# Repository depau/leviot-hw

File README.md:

# LevIoT - Air Purifier replacement controller

This is a replacement PCB based on ESP32 for the Levoit "True HEPA Air Purifier" Core 300, (Amazon model number: 817915027059).

It has currently not been tested yet, I just ordered it from a PCB manufacturer.

I spent around 30€ for 5 PCBs with most components pre-soldered by the PCB manufacturer, + around 13€ on AliExpress for the
push buttons, shift registers and PH connectors.

Touchpad springs and LEDs are going to be recovered from the original PCB.

## Taking the original board out

The top cover comes off by inserting a spudger tool between the top white and gray plastic parts.

The PCB is attached to the top plastic lid with some clips, and connected to the motor via a 6-pin JST-PH connector.

## Control board protocol

Pinout:

| Pin #   | Function   |
| ------- | ---------- |
| 1 (red) | VCC        |
| 2       | GND        |
| 3       | Speed 3    |
| 4       | Speed 2    |
| 5       | Speed 1    |
| 6       | Night mode |

The control board simply pulls one of the pins from 3 to 6 high with the other ones low to set the speed, with all low being "off".

The motor side seems to accept pretty much any voltage > 1V as long as the current is at least ~20 mA, though when using the original
board I measure 4V across the pin and ground - current should be around 80 mA.

You can test it by placing a 100 ohm resistor between 5V and one of the speed pins.

### Important safety notice

I'm not an electrical motor expert but I know that fans need to be started at the maximum speed from the off state in order to
prevent motor strain, overheating and fire hazards.

See this video about it by Technology Connections: https://www.youtube.com/watch?v=hQ3GW7lVBWY

A custom board firmware must kickstart the fan at maximum speed for ~1 sec after power on, then set it back to whatever speed
is desired.

The original board does this automatically.

## License

CERN Open Hardware License, strictly reciprocal.

## Disclaimer

I will not take any responsibility for broken air filters caused by modding or installing this custom PCB. You take your own
responsibility.

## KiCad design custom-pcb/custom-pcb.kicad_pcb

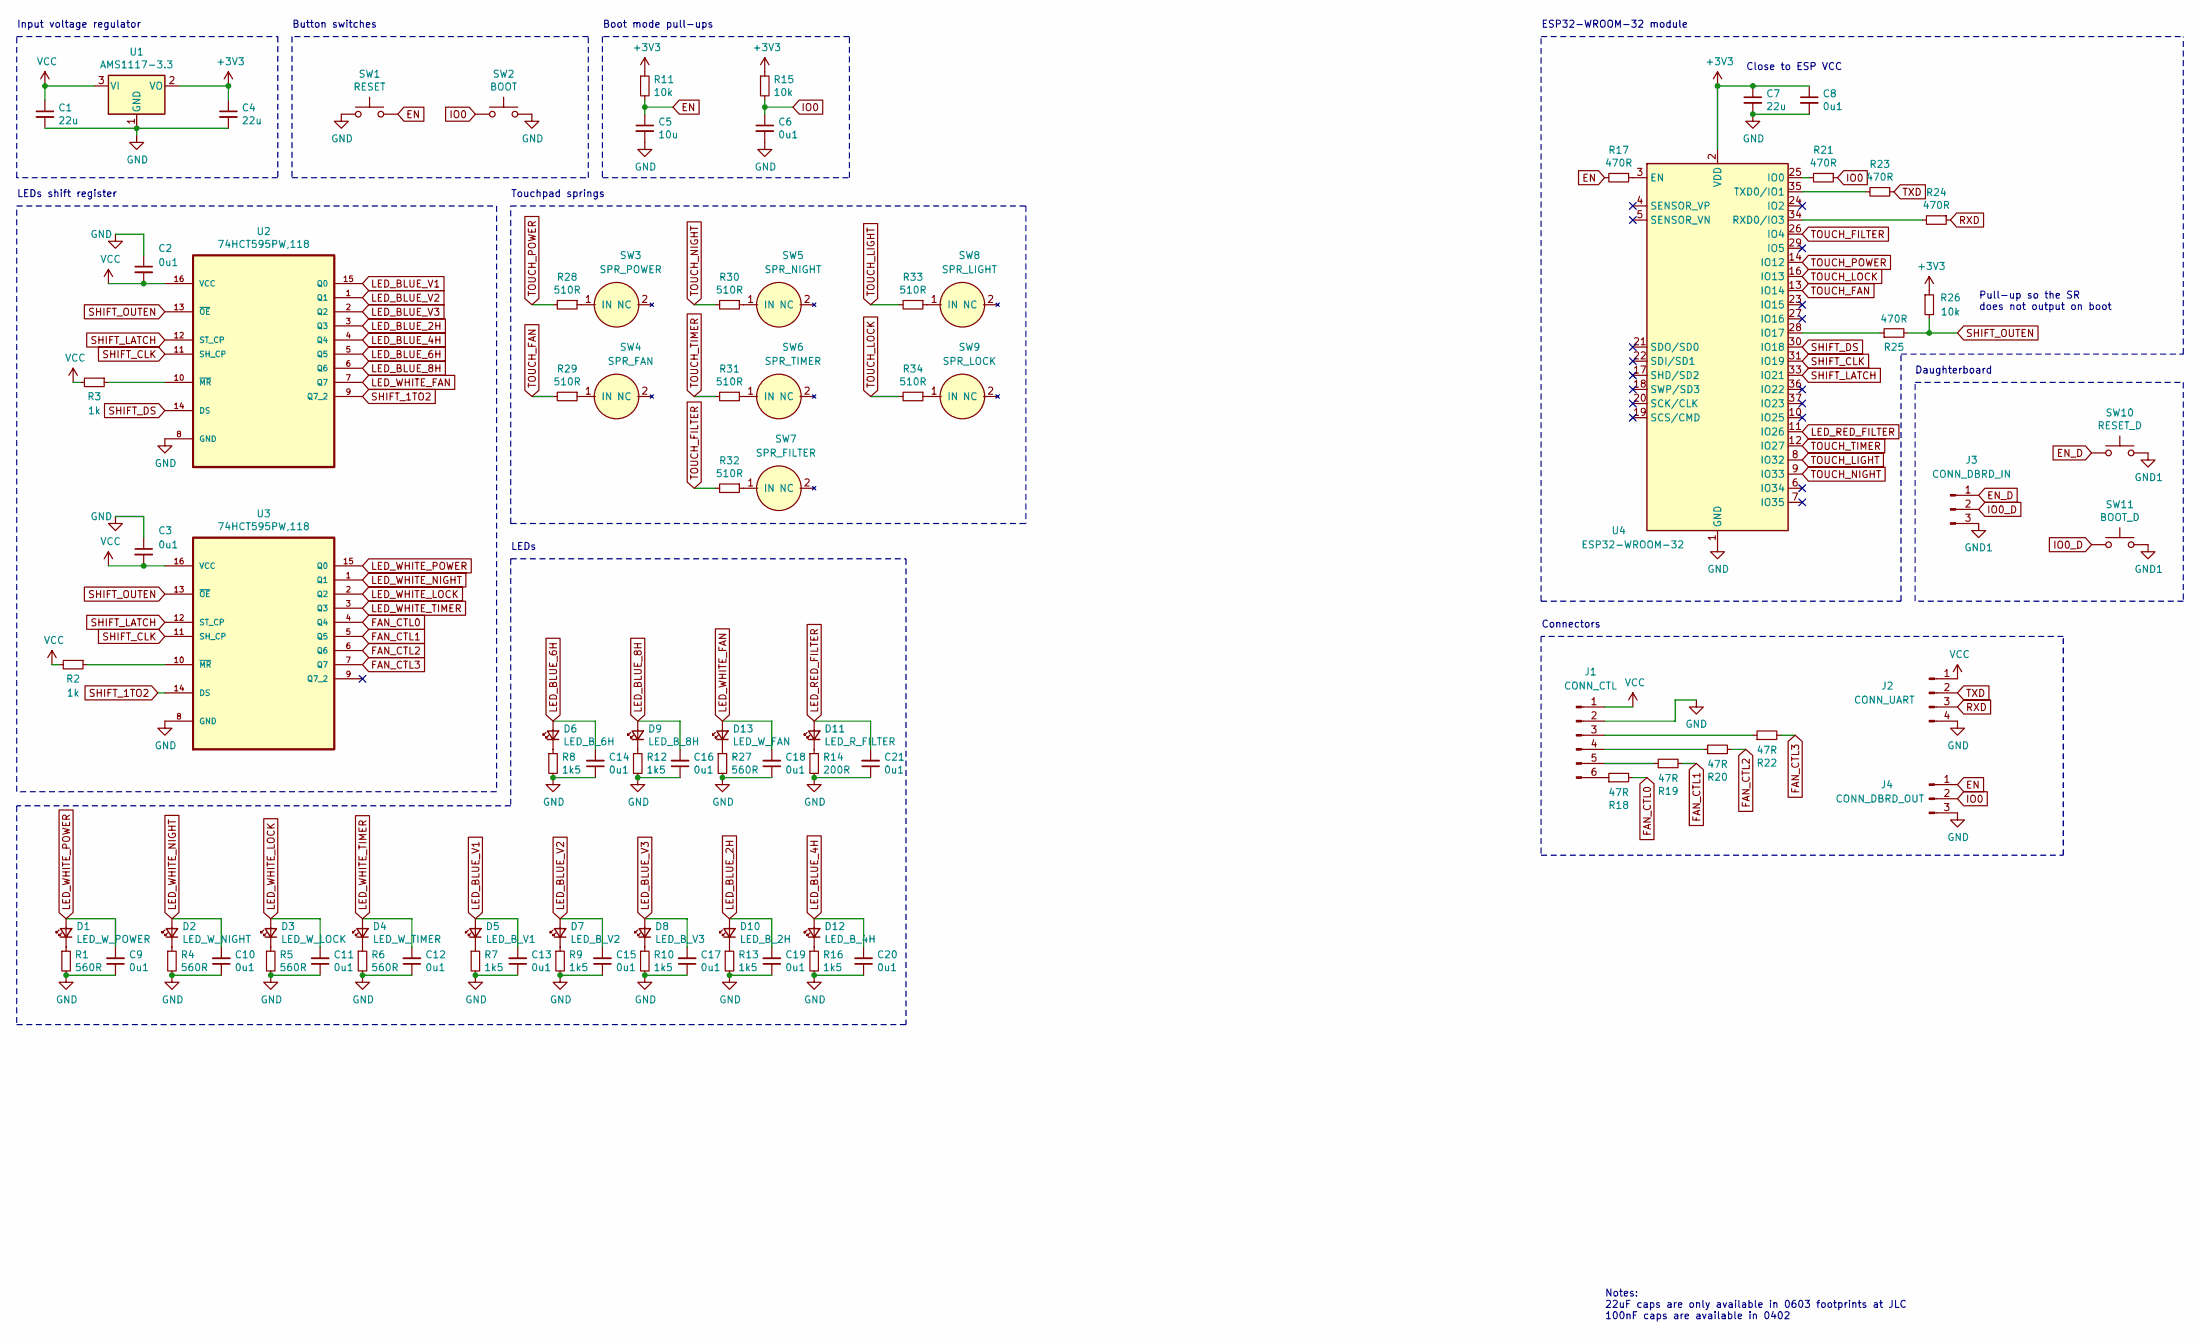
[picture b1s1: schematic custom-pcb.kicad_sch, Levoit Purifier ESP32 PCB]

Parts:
C1, C4, C7: 22u; C_0805_2012Metric; LCSC Part C45783
C2, C3, C8: 0u1; C_0805_2012Metric; LCSC Part C49678
C5: 10u; C_0402_1005Metric; LCSC Part C15525
C6: 0u1; C_0402_1005Metric; LCSC Part C1525
C9, C10, C11, C12, C13, C14, C15, C16, C17, C18, C19, C20, C21: 0u1; C_0402_1005Metric
D1: LED_W_POWER; LED_D5.0mm-centered; JLCPCB BOM 0
D2: LED_W_NIGHT; LED_D5.0mm-centered; JLCPCB BOM 0
D3: LED_W_LOCK; LED_D5.0mm-centered; JLCPCB BOM 0
D4: LED_W_TIMER; LED_D5.0mm-centered; JLCPCB BOM 0
D5: LED_B_V1; LED_0603_1608Metric_Pad1.05x0.95mm_HandSolder; JLCPCB BOM 0
D6: LED_B_6H; LED_0603_1608Metric_Pad1.05x0.95mm_HandSolder; JLCPCB BOM 0
D7: LED_B_V2; LED_0603_1608Metric_Pad1.05x0.95mm_HandSolder; JLCPCB BOM 0
D8: LED_B_V3; LED_0603_1608Metric_Pad1.05x0.95mm_HandSolder; JLCPCB BOM 0
D9: LED_B_8H; LED_0603_1608Metric_Pad1.05x0.95mm_HandSolder; JLCPCB BOM 0
D10: LED_B_2H; LED_0603_1608Metric_Pad1.05x0.95mm_HandSolder; JLCPCB BOM 0
D11: LED_R_FILTER; LED_D5.0mm-centered; JLCPCB BOM 0
D12: LED_B_4H; LED_0603_1608Metric_Pad1.05x0.95mm_HandSolder; JLCPCB BOM 0
D13: LED_W_FAN; LED_D5.0mm-centered; JLCPCB BOM 0
J1: CONN_CTL; JST_PH_B6B-PH-K_1x06_P2.00mm_Vertical; JLCPCB BOM 0
J2: CONN_UART; PinHeader_1x04_P2.54mm_Vertical; JLCPCB BOM 0
J3: CONN_DBRD_IN; PinHeader_1x03_P2.54mm_Vertical; JLCPCB BOM 0
J4: CONN_DBRD_OUT; PinHeader_1x03_P2.54mm_Vertical; JLCPCB BOM 0
R1, R4, R5, R6, R27: 560R; R_0603_1608Metric; LCSC Part C23204
R2, R3: 1k; R_0402_1005Metric; LCSC Part C11702
R7, R8, R9, R10, R12, R13, R16: 1k5; R_0402_1005Metric; LCSC Part C25867
R11, R15, R26: 10k; R_0402_1005Metric; LCSC Part C25744
R14: 200R; R_0402_1005Metric; LCSC Part C25087
R17, R21, R23, R24, R25: 470R; R_0402_1005Metric; LCSC Part C25117
R18, R19, R20, R22: 47R; R_0402_1005Metric; LCSC Part C25118
R28, R29, R30, R31, R32, R33, R34: 510R; R_0402_1005Metric; LCSC Part C25125
SW1: RESET; Tactile_Push_Button_SMD_3x3x1.5mm.kicad_mod; JLCPCB BOM 0
SW2: BOOT; Tactile_Push_Button_SMD_3x3x1.5mm.kicad_mod; JLCPCB BOM 0
SW3: SPR_POWER; touchpad_spring; JLCPCB BOM 0
SW4: SPR_FAN; touchpad_spring; JLCPCB BOM 0
SW5: SPR_NIGHT; touchpad_spring; JLCPCB BOM 0
SW6: SPR_TIMER; touchpad_spring; JLCPCB BOM 0
SW7: SPR_FILTER; touchpad_spring; JLCPCB BOM 0
SW8: SPR_LIGHT; touchpad_spring; JLCPCB BOM 0
SW9: SPR_LOCK; touchpad_spring; JLCPCB BOM 0
SW10: RESET_D; Tactile_Push_Button_SMD_3x3x1.5mm.kicad_mod; JLCPCB BOM 0
SW11: BOOT_D; Tactile_Push_Button_SMD_3x3x1.5mm.kicad_mod; JLCPCB BOM 0
U1: AMS1117-3.3; SOT-223-3_TabPin2; LCSC Part C6186
U2, U3: 74HCT595PW,118; TSSOP-16_4.4x5mm_P0.65mm; MPN 74HC595D,118; LCSC Part C99710
U4: ESP32-WROOM-32; LCSC Part C701343

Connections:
+3V3: C4.1, C7.1, C8.1, R11.1, R15.1, R26.1, U1.2 (VO), U4.2 (VDD)
EN: C5.1, J4.1, R11.2, R17.2, SW1.2
EN_D: J3.1, SW10.1
FAN_CTL0: R18.2, U3.4 (Q4)
FAN_CTL1: R19.2, U3.5 (Q5)
FAN_CTL2: R20.2, U3.6 (Q6)
FAN_CTL3: R22.2, U3.7 (Q7)
GND: C1.2, C2.1, C3.1, C4.2, C5.2, C6.2, C7.2, C8.2, C9.1, C10.1, C11.1, C12.1, C13.1, C14.1, C15.1, C16.1, C17.1, C18.1, C19.1, C20.1, C21.1, J1.2, J2.4, J4.3, R1.2, R4.2, R5.2, R6.2, R7.2, R8.2, R9.2, R10.2, R12.2, R13.2, R14.2, R16.2, R27.2, SW1.1, SW2.2, U1.1 (GND), U2.8 (GND), U3.8 (GND), U4.1 (GND), U4.15 (GND), U4.38 (GND), U4.39 (GND)
GND1: J3.3, SW10.2, SW11.2
IO0: C6.1, J4.2, R15.2, R21.1, SW2.1
IO0_D: J3.2, SW11.1
LED_BLUE_2H: C19.2, D10.2 (A), U2.3 (Q3)
LED_BLUE_4H: C20.2, D12.2 (A), U2.4 (Q4)
LED_BLUE_6H: C14.2, D6.2 (A), U2.5 (Q5)
LED_BLUE_8H: C16.2, D9.2 (A), U2.6 (Q6)
LED_BLUE_V1: C13.2, D5.2 (A), U2.15 (Q0)
LED_BLUE_V2: C15.2, D7.2 (A), U2.1 (Q1)
LED_BLUE_V3: C17.2, D8.2 (A), U2.2 (Q2)
LED_RED_FILTER: C21.2, D11.2 (A), U4.11 (IO26)
LED_WHITE_FAN: C18.2, D13.2 (A), U2.7 (Q7)
LED_WHITE_LOCK: C11.2, D3.2 (A), U3.2 (Q2)
LED_WHITE_NIGHT: C10.2, D2.2 (A), U3.1 (Q1)
LED_WHITE_POWER: C9.2, D1.2 (A), U3.15 (Q0)
LED_WHITE_TIMER: C12.2, D4.2 (A), U3.3 (Q3)
unnamed: D1.1 (K), R1.1
unnamed: D2.1 (K), R4.1
unnamed: D3.1 (K), R5.1
unnamed: D4.1 (K), R6.1
unnamed: D5.1 (K), R7.1
unnamed: D6.1 (K), R8.1
unnamed: D7.1 (K), R9.1
unnamed: D8.1 (K), R10.1
unnamed: D9.1 (K), R12.1
unnamed: D10.1 (K), R13.1
unnamed: D11.1 (K), R14.1
unnamed: D12.1 (K), R16.1
unnamed: D13.1 (K), R27.1
unnamed: J1.3, R22.1
unnamed: J1.4, R20.1
unnamed: J1.5, R19.1
unnamed: J1.6, R18.1
unnamed: R2.1, U3.10 (~MR)
unnamed: R3.1, U2.10 (~MR)
unnamed: R17.1, U4.3 (EN)
unnamed: R21.2, U4.25 (IO0)
unnamed: R23.2, U4.35 (TXD0/IO1)
unnamed: R24.2, U4.34 (RXD0/IO3)
unnamed: R25.1, U4.28 (IO17)
unnamed: R28.1, SW3.1 (IN)
unnamed: R29.1, SW4.1 (IN)
unnamed: R30.1, SW5.1 (IN)
unnamed: R31.1, SW6.1 (IN)
unnamed: R32.1, SW7.1 (IN)
unnamed: R33.1, SW8.1 (IN)
unnamed: R34.1, SW9.1 (IN)
RXD: J2.3, R24.1
SHIFT_1TO2: U2.9 (Q7_2), U3.14 (DS)
SHIFT_CLK: U2.11 (SH_CP), U3.11 (SH_CP), U4.31 (IO19)
SHIFT_DS: U2.14 (DS), U4.30 (IO18)
SHIFT_LATCH: U2.12 (ST_CP), U3.12 (ST_CP), U4.33 (IO21)
SHIFT_OUTEN: R25.2, R26.2, U2.13 (~OE), U3.13 (~OE)
TOUCH_FAN: R29.2, U4.13 (IO14)
TOUCH_FILTER: R32.2, U4.26 (IO4)
TOUCH_LIGHT: R33.2, U4.8 (IO32)
TOUCH_LOCK: R34.2, U4.16 (IO13)
TOUCH_NIGHT: R30.2, U4.9 (IO33)
TOUCH_POWER: R28.2, U4.14 (IO12)
TOUCH_TIMER: R31.2, U4.12 (IO27)
TXD: J2.2, R23.1
VCC: C1.1, C2.2, C3.2, J1.1, J2.1, R2.2, R3.2, U1.3 (VI), U2.16 (VCC), U3.16 (VCC)

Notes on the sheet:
Input voltage regulator
LEDs shift register
Button switches
Touchpad springs
LEDs
Boot mode pull-ups
ESP32-WROOM-32 module
Connectors
Notes: 22uF caps are only available in 0603 footprints at JLC 100nF caps are available in 0402
Close to ESP VCC
Pull-up so the SR does not output on boot
Daughterboard

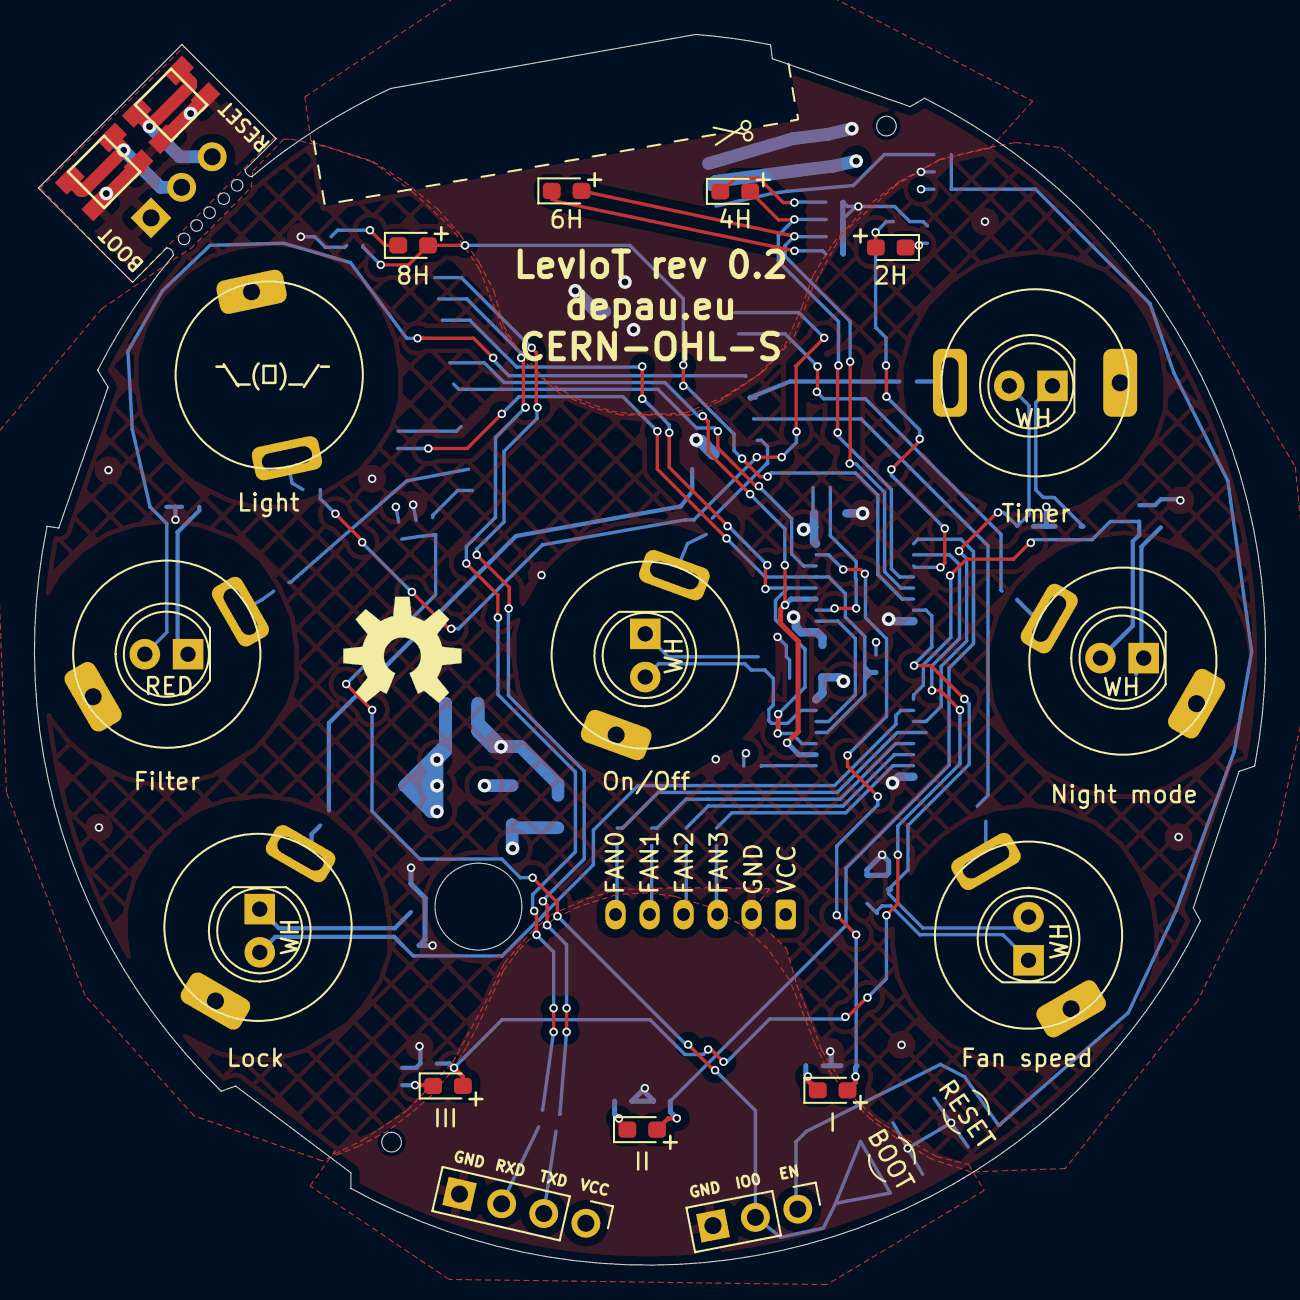
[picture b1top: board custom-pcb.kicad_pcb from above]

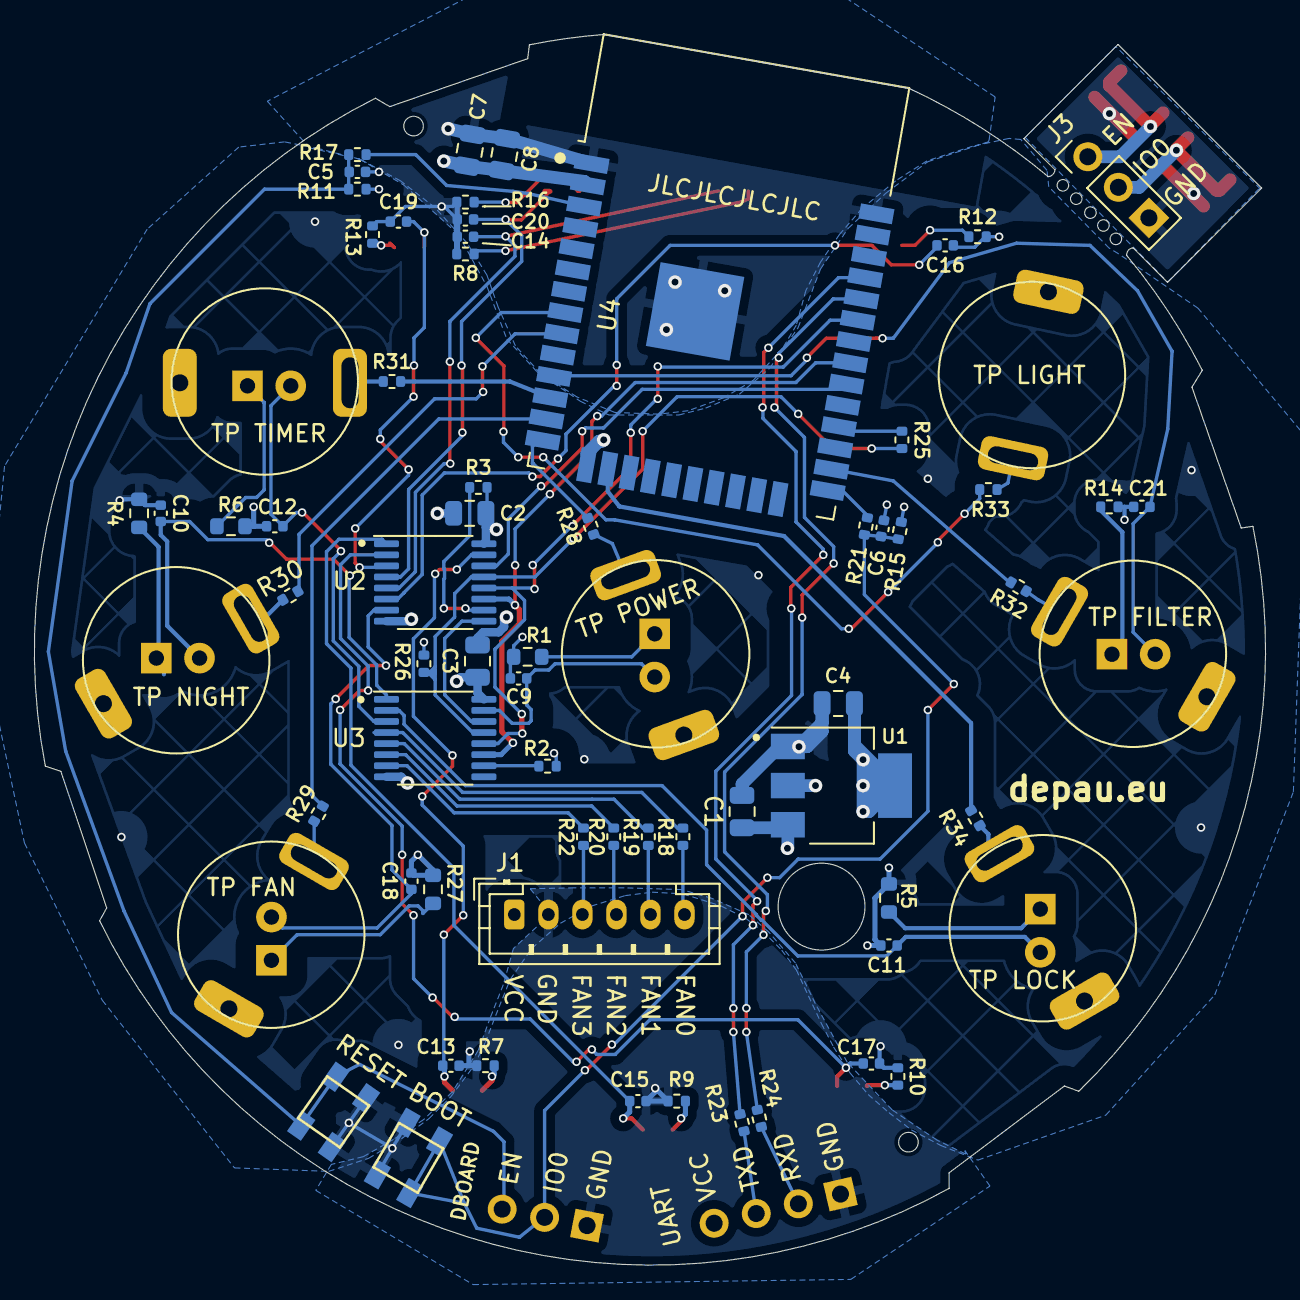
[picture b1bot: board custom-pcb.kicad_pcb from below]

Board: 4 copper layers, 72.4 x 72.3 mm, 88 parts (63 on the bottom side), 70 nets.

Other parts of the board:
board_alignments: LEVOIT_CTL_BOARD_ALIGN; board-alignments

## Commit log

2021-04-14 Add picture
2021-05-09 Connect unconnected pads
2021-05-18 Increase EN capacitor value
2021-05-18 Add LED filter caps and touchpad series res
2021-05-18 Change blue LED footprints to SMD
2021-09-07 Latest changes

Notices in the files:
custom-pcb/custom-pcb.kicad_pcb:
CERN-OHL-S
